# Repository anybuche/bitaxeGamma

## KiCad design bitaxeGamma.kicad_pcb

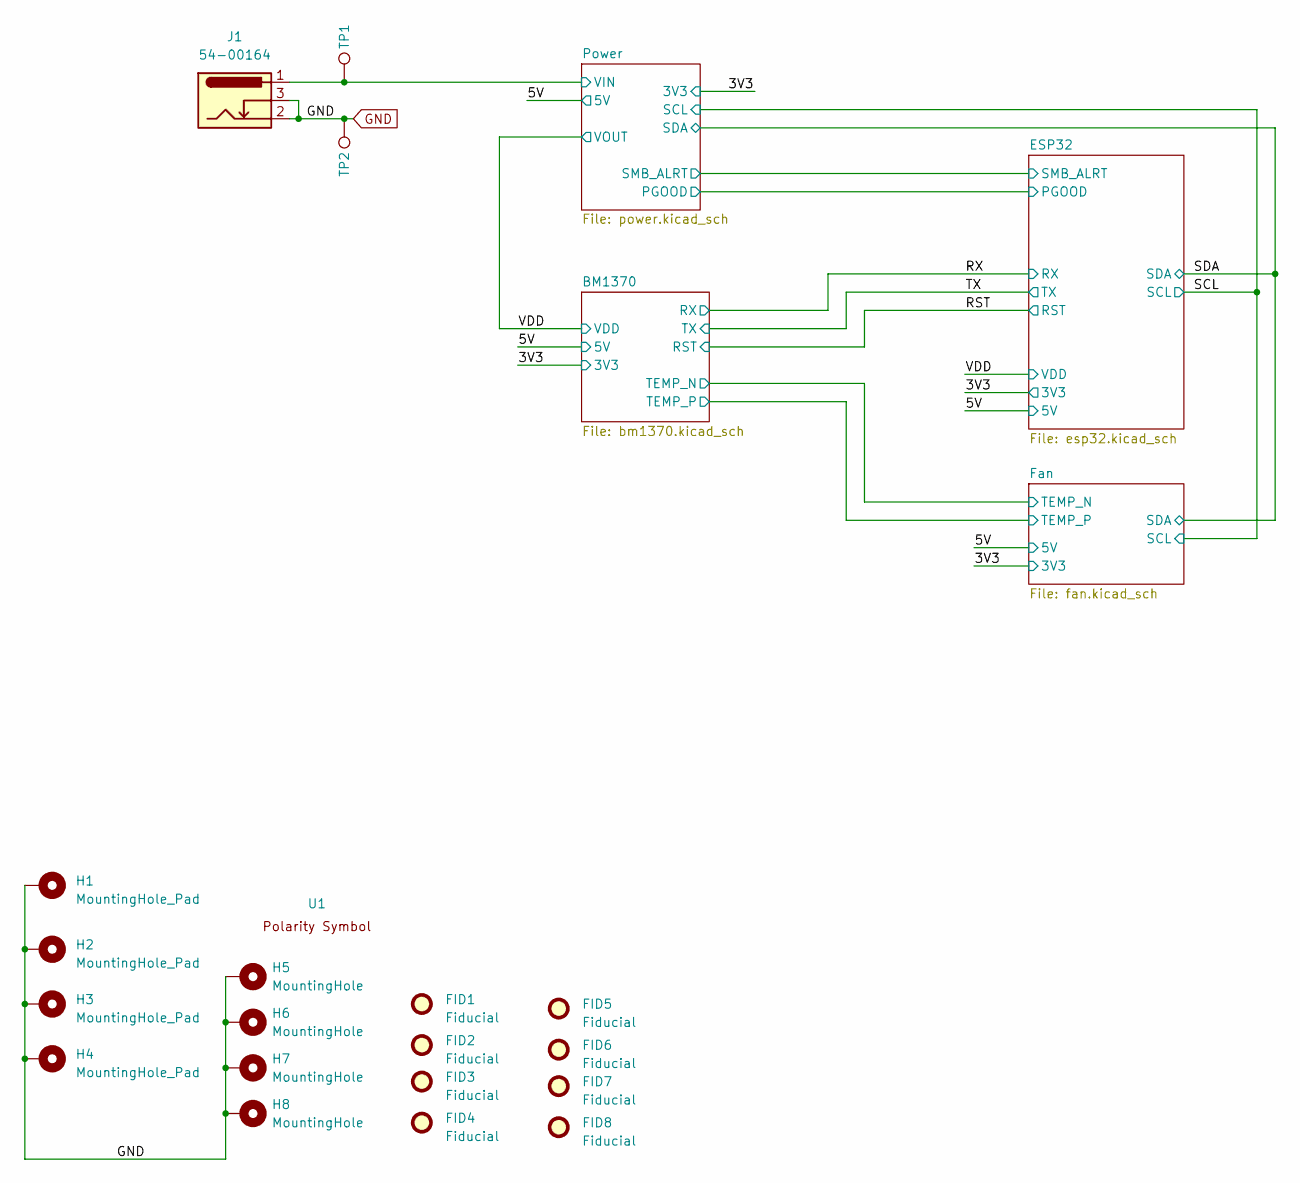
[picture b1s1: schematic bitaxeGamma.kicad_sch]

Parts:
FID1, FID2, FID3, FID4, FID5, FID6, FID7, FID8: Fiducial; Fiducial_1mm_Mask2mm
H1, H2, H3, H4: MountingHole_Pad; MountingHole_3mm_Pad_Via
H5, H6, H7, H8: MountingHole; MountingHole_3mm_Pad
J1: 54-00164; TENSILITY_54-00164; MPN 54-00164; LCSC C431534
TP1, TP2: TestPoint; TestPoint_Pad_D1.5mm
U1: polarity

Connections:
/5V: J1.1, TP1.1; also elsewhere on the board

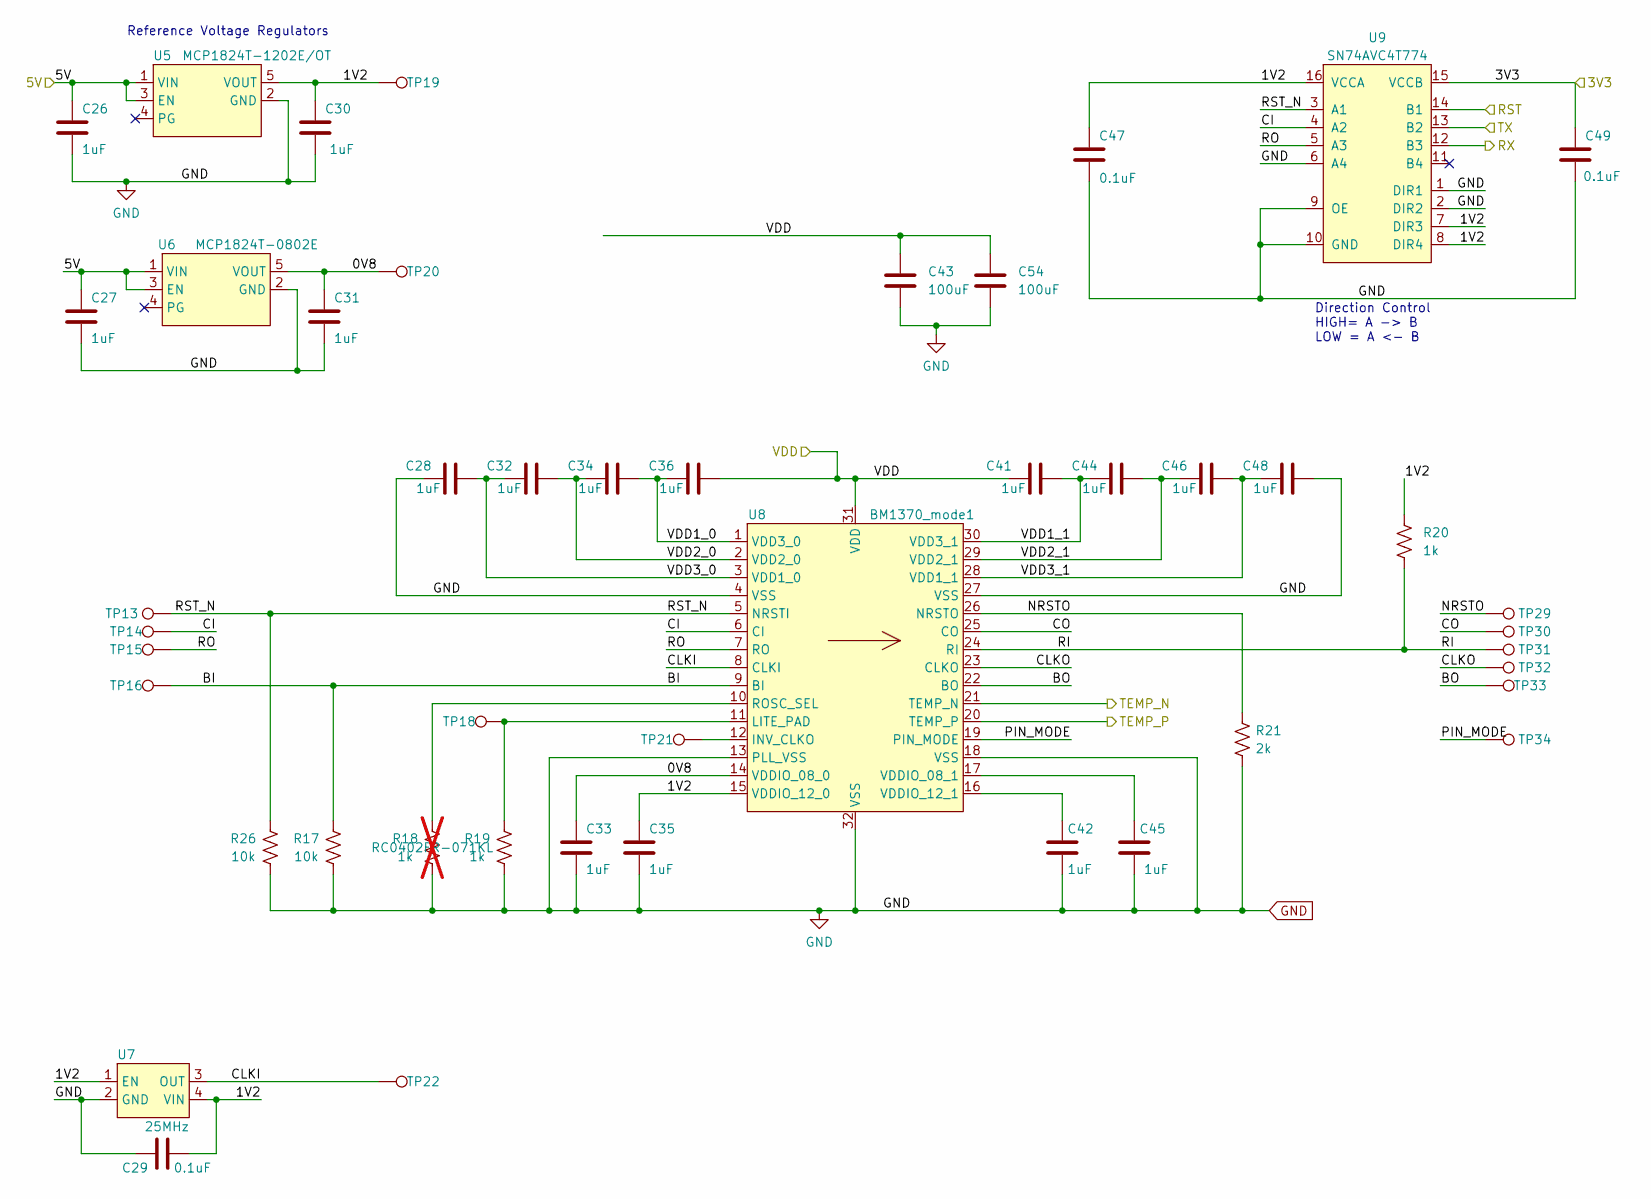
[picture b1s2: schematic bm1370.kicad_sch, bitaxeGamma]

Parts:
C26, C27, C28, C30, C31, C32, C33, C34, C35, C36, C41, C42, C44, C45, C46, C48: 1uF; C_0402_1005Metric; MPN EMK105BJ105MV-F
C29, C47, C49: 0.1uF; C_0402_1005Metric; MPN CL05A104KO5NNNC
C43, C54: 100uF; C_1206_3216Metric; MPN CL31A107MQHNNNE
R17, R26: 10k; R_0402_1005Metric; MPN RC0402FR-0710KL
R18: 1k; R_0402_1005Metric; MPN RC0402FR-071KL; not fitted
R19, R20: 1k; R_0402_1005Metric; MPN RC0402FR-071KL
R21: 2k; R_0402_1005Metric; MPN RC0402FR-072KL
TP13, TP14, TP15, TP16, TP18, TP19, TP20, TP21, TP22, TP29, TP30, TP31, TP32, TP33, TP34: TestPoint; TestPoint_Pad_D1.5mm
U5: MCP1824T-1202E/OT; SOT-23-5; MPN MCP1824T-1202E/OT
U6: MCP1824T-0802E; SOT-23-5; MPN MCP1824T-0802E/OT
U7: 25MHz; SMD3225-4P; MPN SX3M25.000E20F30THN; LCSC C5137262
U8: BM1370_mode1; BM1370
U9: SN74AVC4T774; TSSOP-16_4.4x5mm_P0.65mm; MPN SN74AVC4T774PWR

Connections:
/3V3: C49.1, U9.15 (VCCB); also elsewhere on the board
/5V: C26.1, C27.1, U5.1 (VIN), U5.3 (EN), U6.1 (VIN), U6.3 (EN); also elsewhere on the board
/BM1370/0V8: C31.1, C33.1, TP20.1, U6.5 (VOUT), U8.14 (VDDIO_08_0)
/BM1370/1V2: C29.2, C30.1, C35.1, C47.1, R20.1, TP19.1, U5.5 (VOUT), U7.1 (EN), U7.4 (VIN), U8.15 (VDDIO_12_0), U9.7 (DIR3), U9.8 (DIR4), U9.16 (VCCA)
/BM1370/BI: R17.2, TP16.1, U8.9 (BI)
/BM1370/BO: TP33.1, U8.22 (BO)
/BM1370/CI: TP14.1, U8.6 (CI), U9.4 (A2)
/BM1370/CLKI: TP22.1, U7.3 (OUT), U8.8 (CLKI)
/BM1370/CLKO: TP32.1, U8.23 (CLKO)
/BM1370/CO: TP30.1, U8.25 (CO)
/BM1370/NRSTO: R21.1, TP29.1, U8.26 (NRSTO)
/BM1370/PIN_MODE: TP34.1, U8.19 (PIN_MODE)
/BM1370/RI: R20.2, TP31.1, U8.24 (RI)
/BM1370/RO: TP15.1, U8.7 (RO), U9.5 (A3)
/BM1370/RST_N: R26.2, TP13.1, U8.5 (NRSTI), U9.3 (A1)
/BM1370/VDD1_0: C34.2, C36.1, U8.1 (VDD3_0)
/BM1370/VDD1_1: C41.2, C44.1, U8.30 (VDD3_1)
/BM1370/VDD2_0: C32.2, C34.1, U8.2 (VDD2_0)
/BM1370/VDD2_1: C44.2, C46.1, U8.29 (VDD2_1)
/BM1370/VDD3_0: C28.2, C32.1, U8.3 (VDD1_0)
/BM1370/VDD3_1: C46.2, C48.1, U8.28 (VDD1_1)
/Fan/TEMP_N: U8.21 (TEMP_N); also elsewhere on the board
/Fan/TEMP_P: U8.20 (TEMP_P); also elsewhere on the board
/RST: U9.14 (B1); also elsewhere on the board
/RX: U9.12 (B3); also elsewhere on the board
/TX: U9.13 (B2); also elsewhere on the board
/VDD: C36.2, C41.1, C43.1, C54.1, U8.31 (VDD); also elsewhere on the board
unnamed: TP21.1, U8.12 (INV_CLKO)
unnamed: R19.2, TP18.1, U8.11 (LITE_PAD)
unnamed: C45.1, U8.17 (VDDIO_08_1)
unnamed: C42.1, U8.16 (VDDIO_12_1)

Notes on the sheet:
Reference Voltage Regulators
Direction Control HIGH= A -> B LOW = A <- B

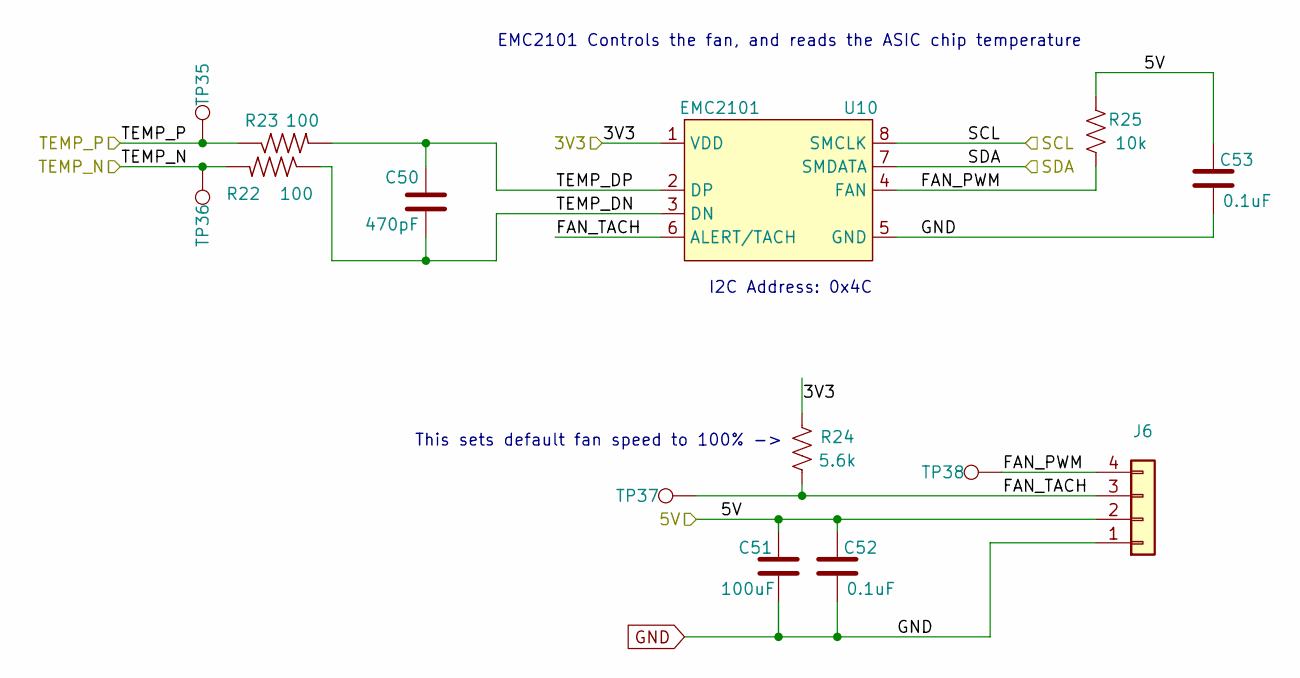
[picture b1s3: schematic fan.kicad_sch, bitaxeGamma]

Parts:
C50: 470pF; C_0402_1005Metric; MPN CL05B471KB5NNNC
C51: 100uF; C_1206_3216Metric; MPN CL31A107MQHNNNE
C52, C53: 0.1uF; C_0402_1005Metric; MPN CL05A104KO5NNNC
J6: Conn_01x04; 470531000; MPN 0470531000
R22, R23: 100; R_0402_1005Metric; MPN RC0402FR-07100RL
R24: 5.6k; R_0402_1005Metric; MPN RC0402FR-135K6L
R25: 10k; R_0402_1005Metric; MPN RC0402FR-0710KL
TP35, TP36, TP37, TP38: TestPoint; TestPoint_Pad_D1.5mm
U10: EMC2101; TSSOP-8_3x3mm_P0.65mm; MPN EMC2101-R-ACZL-TR

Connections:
/3V3: R24.2, U10.1 (VDD); also elsewhere on the board
/5V: C51.1, C52.1, C53.1, J6.2, R25.2; also elsewhere on the board
/Fan/FAN_PWM: J6.4, R25.1, TP38.1, U10.4 (FAN)
/Fan/FAN_TACH: J6.3, R24.1, TP37.1, U10.6 (ALERT/TACH)
/Fan/TEMP_DN: C50.2, R22.1, U10.3 (DN)
/Fan/TEMP_DP: C50.1, R23.2, U10.2 (DP)
/Fan/TEMP_N: R22.2, TP36.1; also elsewhere on the board
/Fan/TEMP_P: R23.1, TP35.1; also elsewhere on the board
/SCL: U10.8 (SMCLK); also elsewhere on the board
/SDA: U10.7 (SMDATA); also elsewhere on the board

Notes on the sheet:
EMC2101 Controls the fan, and reads the ASIC chip temperature
This sets default fan speed to 100% ->
I2C Address: 0x4C

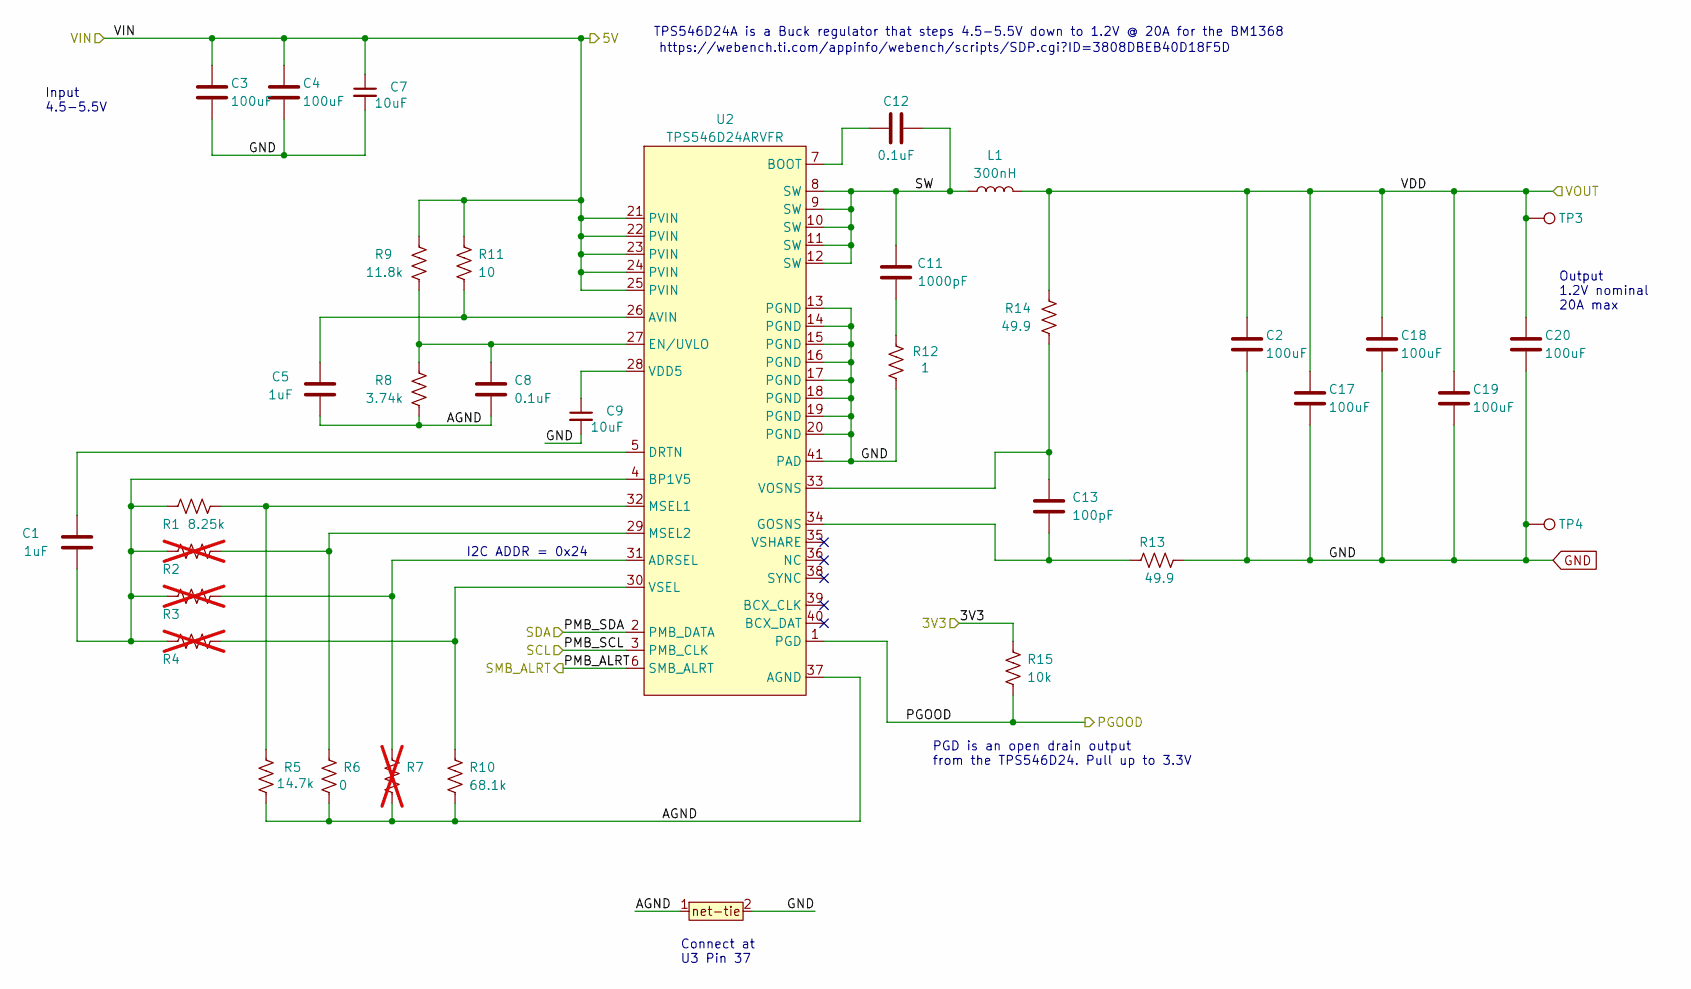
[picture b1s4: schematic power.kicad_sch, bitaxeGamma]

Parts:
C1, C5: 1uF; C_0402_1005Metric; MPN EMK105BJ105MV-F
C2, C3, C4, C17, C18, C19, C20: 100uF; C_1206_3216Metric; MPN CL31A107MQHNNNE
C7, C9: 10uF; C_0603_1608Metric; MPN GRM188R61E106KA73D
C8, C12: 0.1uF; C_0402_1005Metric; MPN CL05A104KO5NNNC
C11: 1000pF; C_0805_2012Metric; MPN CC0805KRX7R9BB102
C13: 100pF; C_0402_1005Metric; MPN 885012005013
L1: 300nH; SLC1175-271MEC_COC; MPN 744308033
R1: 8.25k; R_0402_1005Metric; MPN RC0402FR-078K25L
R2, R3, R4, R7: R_0402_1005Metric; not fitted
R5: 14.7k; R_0402_1005Metric; MPN RC0402FR-0714K7L
R6: 0; R_0402_1005Metric; MPN RC0402FR-070RL
R8: 3.74k; R_0402_1005Metric; MPN RC0402FR-073K74L
R9: 11.8k; R_0402_1005Metric; MPN RC0402FR-0711K8L
R10: 68.1k; R_0402_1005Metric; MPN RC0402FR-0768K1L
R11: 10; R_0402_1005Metric; MPN RC0402FR-0710RL
R12: 1; R_1206_3216Metric; MPN CSR1206FT1R00
R13, R14: 49.9; R_0402_1005Metric; MPN RC0402FR-0749R9L
R15: 10k; R_0402_1005Metric; MPN RC0402FR-0710KL
T1: net-tie; NetTie-0.25mm; MPN 2R5TPE220MAFB
TP3, TP4: TestPoint; TestPoint_Pad_D1.5mm
U2: TPS546D24ARVFR; LQFN40-CLIP; MPN TPS546D24ARVFR

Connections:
/3V3: R15.2; also elsewhere on the board
/5V: C3.1, C4.1, C7.1, R9.1, R11.1, U2.21 (PVIN), U2.22 (PVIN), U2.23 (PVIN), U2.24 (PVIN), U2.25 (PVIN); also elsewhere on the board
/Power/PGOOD: R15.1, U2.1 (PGD); also elsewhere on the board
/Power/PMB_ALRT: U2.6 (SMB_ALRT); also elsewhere on the board
/Power/SW: C11.2, C12.2, L1.1, U2.8 (SW), U2.9 (SW), U2.10 (SW), U2.11 (SW), U2.12 (SW)
/SCL: U2.3 (PMB_CLK); also elsewhere on the board
/SDA: U2.2 (PMB_DATA); also elsewhere on the board
/VDD: C2.1, C17.1, C18.1, C19.1, C20.1, L1.2, R14.1, TP3.1; also elsewhere on the board
unnamed: C11.1, R12.2
unnamed: R3.2, R7.1, U2.31 (ADRSEL)
unnamed: C5.2, R11.2, U2.26 (AVIN)
unnamed: C12.1, U2.7 (BOOT)
unnamed: C1.2, R1.1, R2.1, R3.1, R4.1, U2.4 (BP1V5)
unnamed: C1.1, U2.5 (DRTN)
unnamed: C8.1, R8.1, R9.2, U2.27 (EN/UVLO)
unnamed: C13.2, R13.1, U2.34 (GOSNS)
unnamed: R1.2, R5.2, U2.32 (MSEL1)
unnamed: C9.1, U2.28 (VDD5)
unnamed: C13.1, R14.2, U2.33 (VOSNS)
unnamed: R4.2, R10.1, U2.30 (VSEL)

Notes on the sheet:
TPS546D24A is a Buck regulator that steps 4.5-5.5V down to 1.2V @ 20A for the BM1368
https://webench.ti.com/appinfo/webench/scripts/SDP.cgi?ID=3808DBEB40D18F5D
Input 4.5-5.5V
PGD is an open drain output from the TPS546D24. Pull up to 3.3V
I2C ADDR = 0x24
Output 1.2V nominal 20A max
Connect at U3 Pin 37

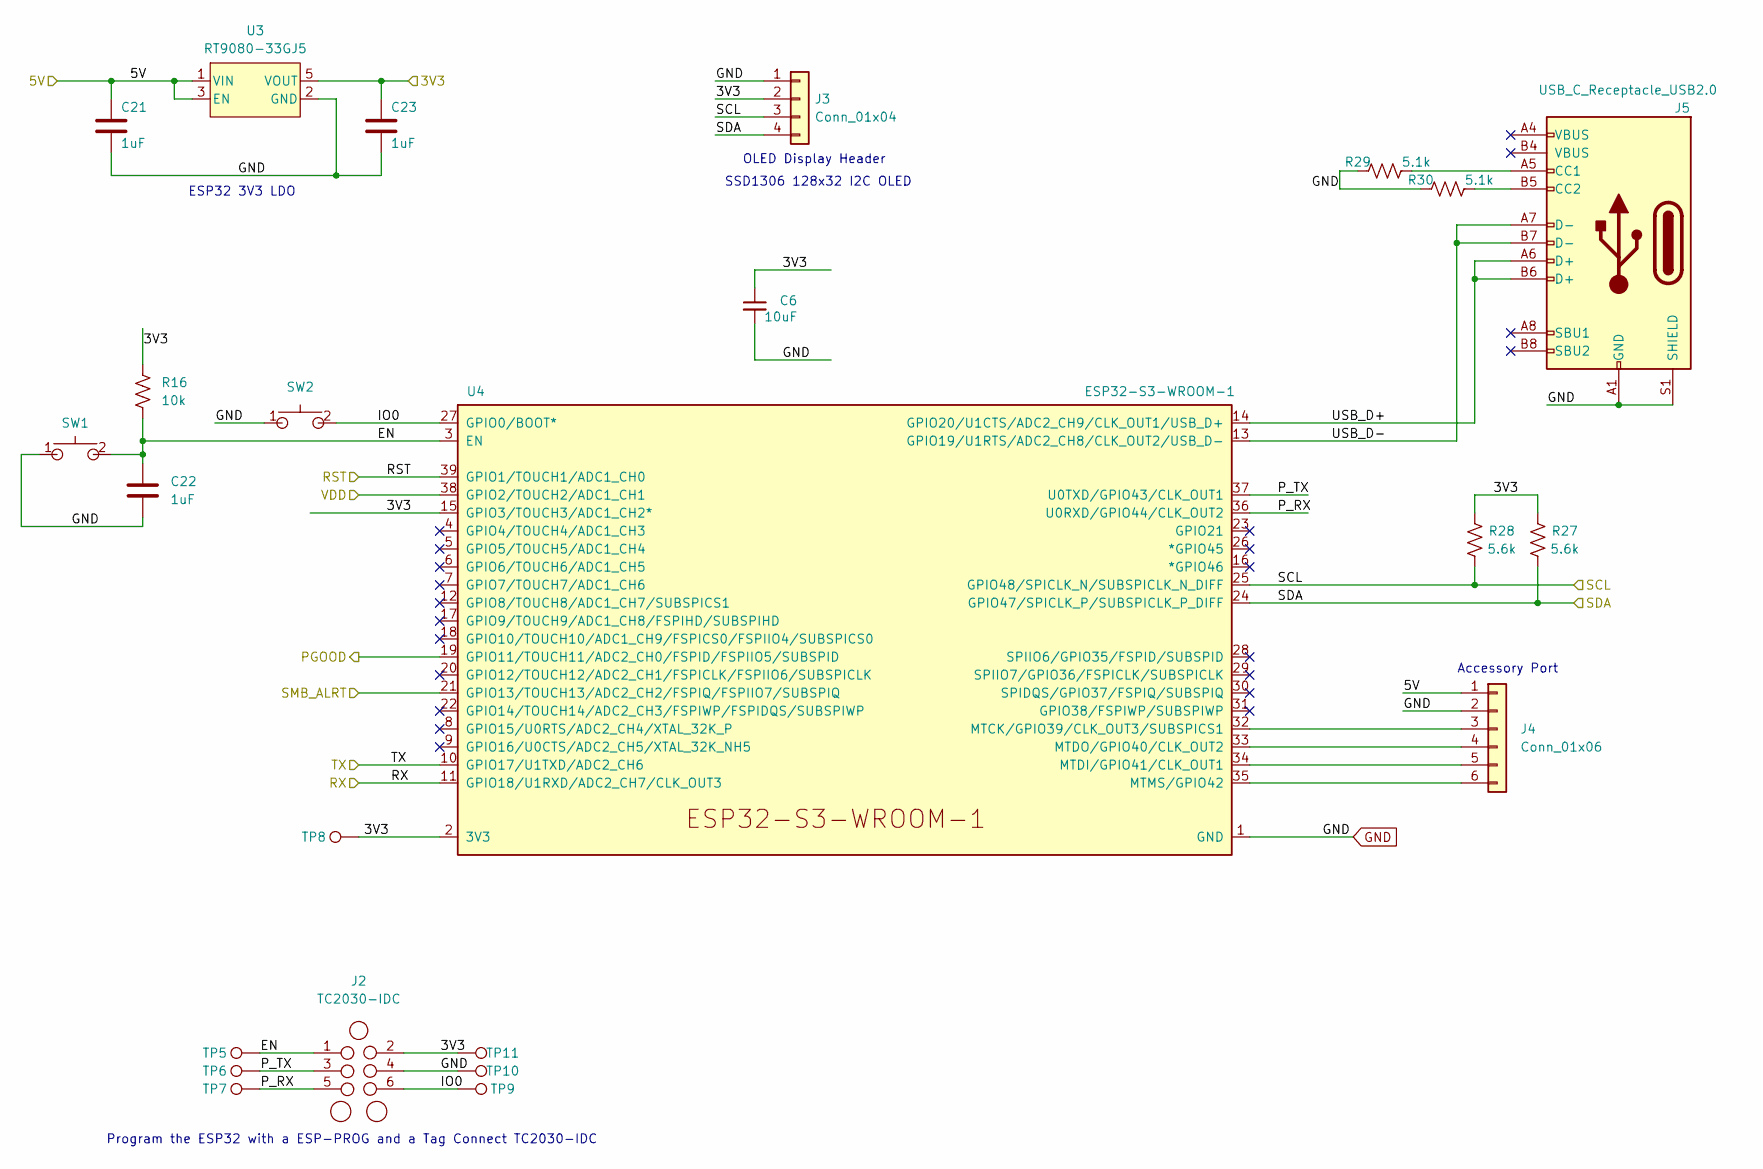
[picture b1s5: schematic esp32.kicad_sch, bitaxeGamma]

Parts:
C6: 10uF; C_0603_1608Metric; MPN GRM188R61E106KA73D
C21, C22, C23: 1uF; C_0402_1005Metric; MPN EMK105BJ105MV-F
J2: TC2030-IDC; Tag-Connect_TC2030-IDC-NL_2x03_P1.27mm_Vertical
J3: Conn_01x04; PinHeader_1x04_P2.54mm_Vertical_shifted
J4: Conn_01x06; PinHeader_1x06_P2.54mm_Vertical
J5: USB_C_Receptacle_USB2.0; USB_C_Receptacle_GCT_USB4105-xx-A; MPN USB4105-GF-A
R16: 10k; R_0402_1005Metric; MPN RC0402FR-0710KL
R27, R28: 5.6k; R_0402_1005Metric; MPN RC0402FR-135K6L
R29, R30: 5.1k; R_0402_1005Metric; MPN RC0402FR-075K1L; LCSC C25905
SW1, SW2: GT-TC029B-H025-L1N; SW_CS1213AGF260_CRS; MPN CS1213AGF260
TP5, TP6, TP7, TP9, TP10, TP11: TestPoint; TestPoint_Pad_D2.5mm
TP8: TestPoint; TestPoint_Pad_D1.5mm
U3: RT9080-33GJ5; MPN RT9080-33GJ5
U4: ESP32-S3-WROOM-1; MPN ESP32-S3-WROOM-1-N16R8

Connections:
/3V3: C6.1, C23.1, J2.2, J3.2, R16.1, R27.2, R28.2, TP8.1, TP11.1, U3.5 (VOUT), U4.2 (3V3), U4.15 (GPIO3/TOUCH3/ADC1_CH2*); also elsewhere on the board
/5V: C21.1, J4.1, U3.1 (VIN), U3.3 (EN); also elsewhere on the board
/ESP32/EN: C22.1, J2.1, R16.2, SW1.2, TP5.1, U4.3 (EN)
/ESP32/IO0: J2.6, SW2.2, TP9.1, U4.27 (GPIO0/BOOT*)
/ESP32/P_RX: J2.5, TP7.1, U4.36 (U0RXD/GPIO44/CLK_OUT2)
/ESP32/P_TX: J2.3, TP6.1, U4.37 (U0TXD/GPIO43/CLK_OUT1)
/ESP32/USB_D+: J5.A6 (D+), J5.B6 (D+), U4.14 (GPIO20/U1CTS/ADC2_CH9/CLK_OUT1/USB_D+)
/ESP32/USB_D-: J5.A7 (D-), J5.B7 (D-), U4.13 (GPIO19/U1RTS/ADC2_CH8/CLK_OUT2/USB_D-)
/Power/PGOOD: U4.19 (GPIO11/TOUCH11/ADC2_CH0/FSPID/FSPIIO5/S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); also elsewhere on the board
/Power/PMB_ALRT: U4.21 (GPIO13/TOUCH13/ADC2_CH2/FSPIQ/FSPIIO7/S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); also elsewhere on the board
/RST: U4.39 (GPIO1/TOUCH1/ADC1_CH0); also elsewhere on the board
/RX: U4.11 (GPIO18/U1RXD/ADC2_CH7/CLK_OUT3); also elsewhere on the board
/SCL: J3.3, R28.1, U4.25 (GPIO48/SPICLK_N/SUBSPICLK_N_DIFF); also elsewhere on the board
/SDA: J3.4, R27.1, U4.24 (GPIO47/SPICLK_P/SUBSPICLK_P_DIFF); also elsewhere on the board
/TX: U4.10 (GPIO17/U1TXD/ADC2_CH6); also elsewhere on the board
/VDD: U4.38 (GPIO2/TOUCH2/ADC1_CH1); also elsewhere on the board
unnamed: J4.3, U4.32 (MTCK/GPIO39/CLK_OUT3/SUBSPICS1)
unnamed: J4.4, U4.33 (MTDO/GPIO40/CLK_OUT2)
unnamed: J4.5, U4.34 (MTDI/GPIO41/CLK_OUT1)
unnamed: J4.6, U4.35 (MTMS/GPIO42)
unnamed: J5.A5 (CC1), R29.2
unnamed: J5.B5 (CC2), R30.2

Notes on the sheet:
Accessory Port
ESP32 3V3 LDO
Program the ESP32 with a ESP-PROG and a Tag Connect TC2030-IDC
SSD1306 128x32 I2C OLED
OLED Display Header

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
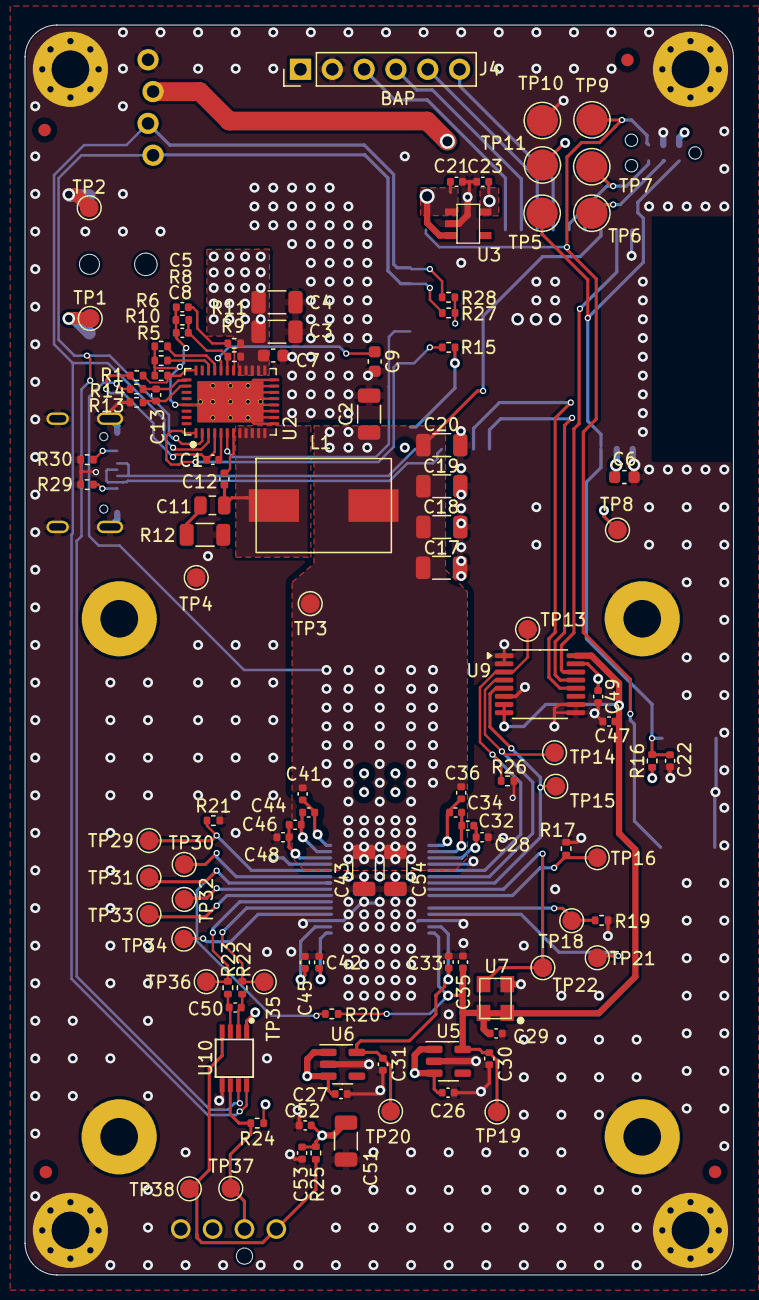
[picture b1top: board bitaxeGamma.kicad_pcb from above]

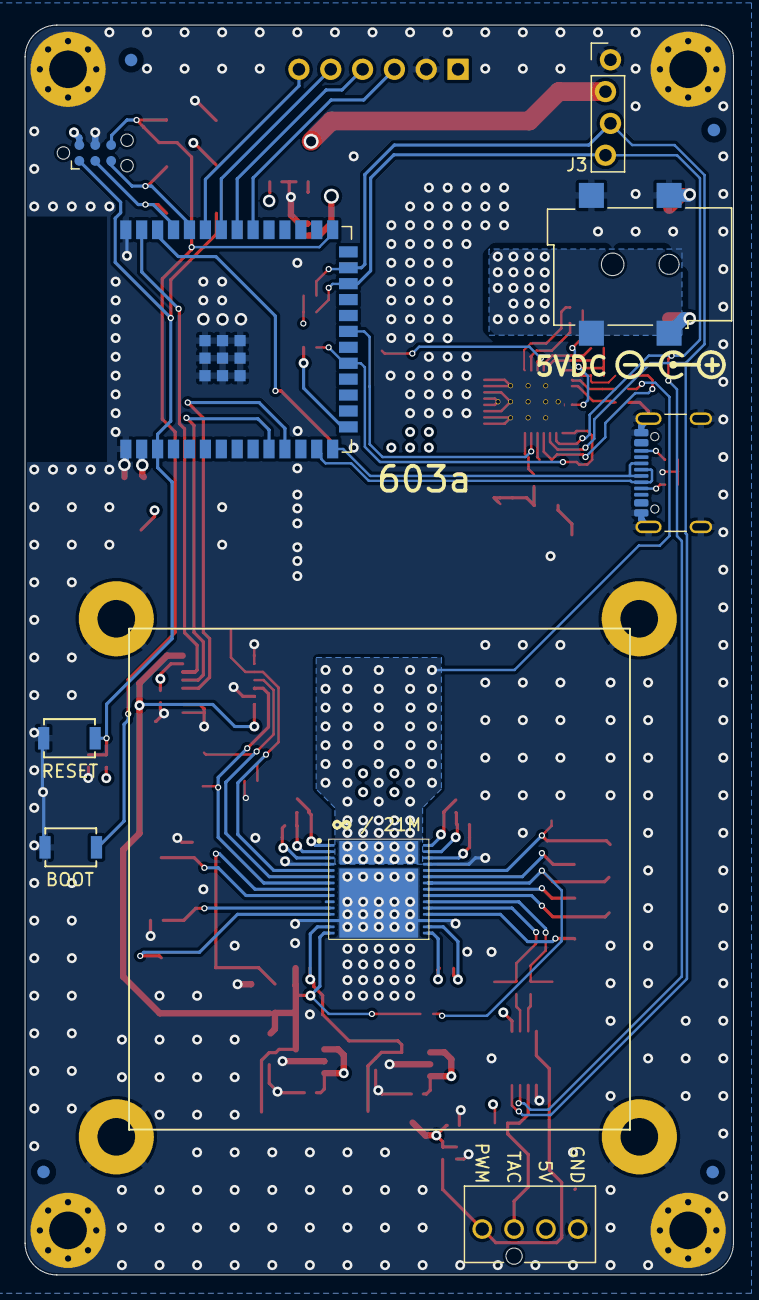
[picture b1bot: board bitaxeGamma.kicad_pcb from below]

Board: 4 copper layers, 56.5 x 99.8 mm, 135 parts (14 on the bottom side), 66 nets.

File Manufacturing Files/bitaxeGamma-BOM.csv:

Reference,Value,Description,Qty,MF,MPN,Alt. MPN,DK,LCSC
C1 C5 C21 C22 C23 C26 C27 C28 C30 C31 C32 C33 C34 C35 C36 C41 C42 C44 C45 C46 C48,1uF,CAP CER 1UF 16V X5R 0402,21,Taiyo Yuden,EMK105BJ105MV-F,,587-5514-1-ND,
C2 C3 C4 C17 C18 C19 C20 C43 C51 C54,100uF,CAP CER 100UF 6.3V X5R 1206,10,Samsung,CL31A107MQHNNNE,,1276-1782-1-ND,
C6 C7 C9,10uF,CAP CER 10UF 25V X5R 0603,3,Murata,GRM188R61E106KA73D,,490-18214-1-ND,
C8 C12 C29 C47 C49 C52 C53,0.1uF,CAP CER 0.1UF 16V X5R 0402,7,Samsung,CL05A104KO5NNNC,,1276-1234-1-ND,
C11,1000pF,CAP CER 1000PF 50V X7R 0805,1,Yageo,CC0805KRX7R9BB102,,311-1127-1-ND,
C13,100pF,CAP CER 100PF 10V C0G/NP0 0402,1,WE,885012005013,,732-7431-1-ND,
C50,470pF,CAP CER 470PF 50V X7R 0402,1,Samsung,CL05B471KB5NNNC,,1276-1566-1-ND,
J1,54-00164,CONN JACK R/A SMT 5.5X2.1MM,1,Tensility,54-00164,,839-54-00164CT-ND,C431534
J5,USB_C_Receptacle_USB2.0,USB Connectors USB Type C,2.0, Rec,SMT, 0.95mmTH Shell Stakes,G/F,RA,Top Mnt,T&R,1,GCT,USB4105-GF-A,,2073-USB4105-GF-ACT-ND,
J6,Conn_01x04,CONN HEADER VERT 4POS 2.54MM,1,Molex,0470531000,,WM4330-ND,
L1,300nH,FIXED IND 330NH 25A 0.00037OHM,1,WE,744308033,104CDMCCDS-R30MC,732-3024-1-ND,
R1,8.25k,RES 8K25 OHM 1% 1/16W 0402,1,Yageo,RC0402FR-078K25L,,311-8.25KLRCT-ND,
R5,14.7k,RES 14K7 OHM 1% 1/16W 0402,1,Yageo,RC0402FR-0714K7L,,YAG2984CT-ND,
R6,0,RES 0R OHM 1% 1/16W 0402,1,Yageo,RC0402FR-070RL,,311-0.0JRCT-ND,
R8,3.74k,RES 3K74 OHM 1% 1/16W 0402,1,Yageo,RC0402FR-073K74L,,311-3.74KLRCT-ND,
R9,11.8k,RES 11K8 OHM 1% 1/16W 0402,1,Yageo,RC0402FR-0711K8L,,YAG2958CT-ND,
R10,68.1k,RES 68K1 OHM 1% 1/16W 0402,1,Yageo,RC0402FR-0768K1L,,YAG3213CT-ND,
R11,10,RES 10R OHM 1% 1/16W 0402,1,Yageo,RC0402FR-0710RL,,311-10.0LRCT-ND,
R12,1,RES 1 OHM 1% 1/2W 1206,1,Stackpole,CSR1206FT1R00,,CSR1206FT1R00CT-ND,
R13 R14,49.9,RES 49R9 OHM 1% 1/2W 1206,2,Yageo,RC0402FR-0749R9L,,311-49.9LRCT-ND,
R15 R16 R17 R25 R26,10k,RES 10K OHM 1% 1/16W 0402,5,Yageo,RC0402FR-0710KL,,311-10KJRCT-ND,
R19 R20,1k,RES 1K OHM 1% 1/16W 0402,2,Yageo,RC0402FR-071KL,,311-1.00KLRCT-ND,
R21,2k,RES 2K OHM 1% 1/16W 0402,1,Yageo,RC0402FR-072KL,,311-2KLRCT-ND,
R22 R23,100,RES 100R OHM 1% 1/16W 0402,2,Yageo,RC0402FR-07100RL,,311-100LRCT-ND,
R24 R27 R28,5.6k,RES 5.6K OHM 1% 1/16W 0402,3,Yageo,RC0402FR-135K6L,,13-RC0402FR-135K6LCT-ND,
R29 R30,5.1k,RES 5.1K OHM 1% 1/16W 0402,2,Yageo,RC0402FR-075K1L,,311-5.10KLRCT-ND,C25905
SW1 SW2,GT-TC029B-H025-L1N,SWITCH TACTILE SPST-NO 0.05A 50V,2,CIT,CS1213AGF260,,2449-CS1213AGF260CT-ND,
U2,TPS546D24ARVFR,Switching Voltage Regulators 2.95-V to 16-V stac kable 40-A synchrono,1,TI,TPS546D24ARVFR,,296-TPS546D24ARVFRCT-ND,
U3,RT9080-33GJ5,IC REG LIN 3.3V 600MA TSOT-23-5,1,Richtek,RT9080-33GJ5,,1028-1509-1-ND,
U4,ESP32-S3-WROOM-1,RF TXRX MOD BT WIFI PCB TH SMD,1,Espressif,ESP32-S3-WROOM-1-N16R8,,1965-ESP32-S3-WROOM-1-N16R8CT-ND,
U5,MCP1824T-1202E/OT,IC REG LINEAR 1.2V 300MA SOT23-5,1,Microchip,MCP1824T-1202E/OT,,MCP1824T-1202E/OTCT-ND,
U6,MCP1824T-0802E,IC REG LINEAR 0.8V 300MA SOT23-5,1,Microchip,MCP1824T-0802E/OT,,MCP1824T-0802E/OTCT-ND,
U7,25MHz,1.2V ±20ppm 2mA ±30ppm 25MHz CMOS SMD3225-4P Crystal Oscillators ROHS,1,SCTF,SX3M25.000E20F30THN,OXLTDLJANF-25.000000,1664-OXLTDLJANF-25.000000CT-ND,C5137262
U8,BM1370_mode1,ASIC,1,,,,,
U9,SN74AVC4T774,Voltage Level Translator Bidirectional 1 Circuit 4 Channel 380Mbps 16-TSSOP,1,TI,SN74AVC4T774PWR,,296-24739-1-ND,
U10,EMC2101,IC FAN CTRLR I2C/SMBUS 8MSOP,1,Microchip,EMC2101-R-ACZL-TR,,EMC2101-R-ACZL-CT-ND,

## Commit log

2025-08-07 Optimize copper pours and routing
2025-08-10 Alin vias and components on the grid
2025-08-10 Add stitching GND vias
2025-08-15 Finish retouches and prepare manufacturing files
2025-08-15 Correct 2 zones
